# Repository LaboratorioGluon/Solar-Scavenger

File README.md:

# Solar Scavenger

Os presento el barco **Solar Scavenger** participante de la VI Regata Solar en Baiona!

El resultado: Primer premio en diseño y tercero en regata!

Todo está desarrollado en directo, desde la PCB, diseño 3D, software y montaje! (Link abajo)

## Materiales usados:

| Nombre | Descripción |
|---|---|
| [A2212 1000 KV](https://s.click.aliexpress.com/e/_DB0ZUoN) | Motor brushless outrunner para el barco|
| [ESC 4S 40A](https://s.click.aliexpress.com/e/_DB3iqU5) | Controlador de velocidad ESC |
| [ESP32](https://s.click.aliexpress.com/e/_DdJJJ5L) | Cerebro del controlador |

## PCB

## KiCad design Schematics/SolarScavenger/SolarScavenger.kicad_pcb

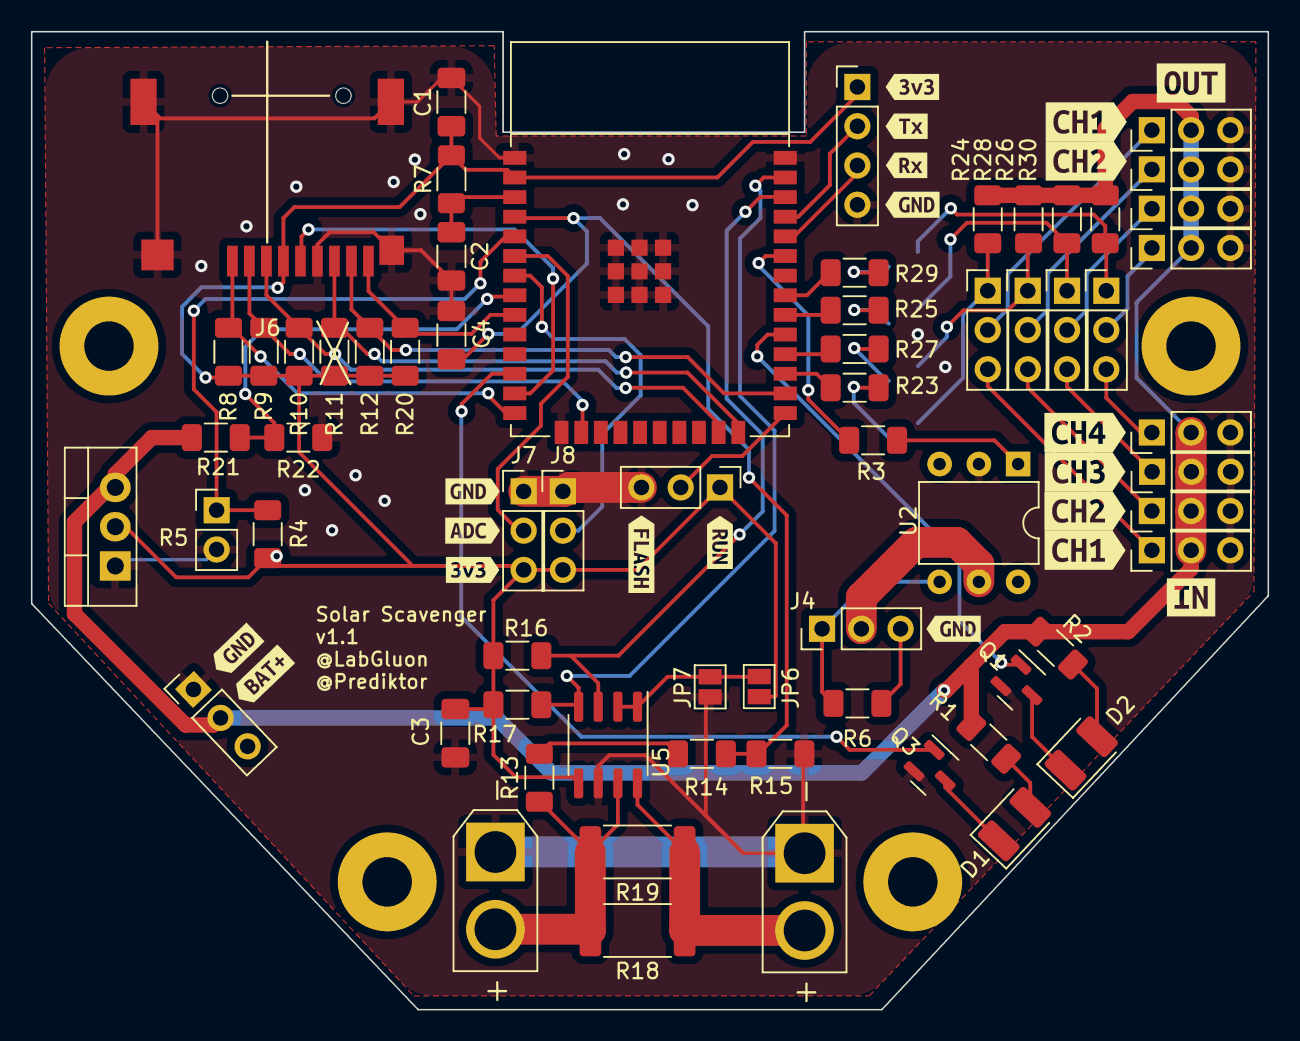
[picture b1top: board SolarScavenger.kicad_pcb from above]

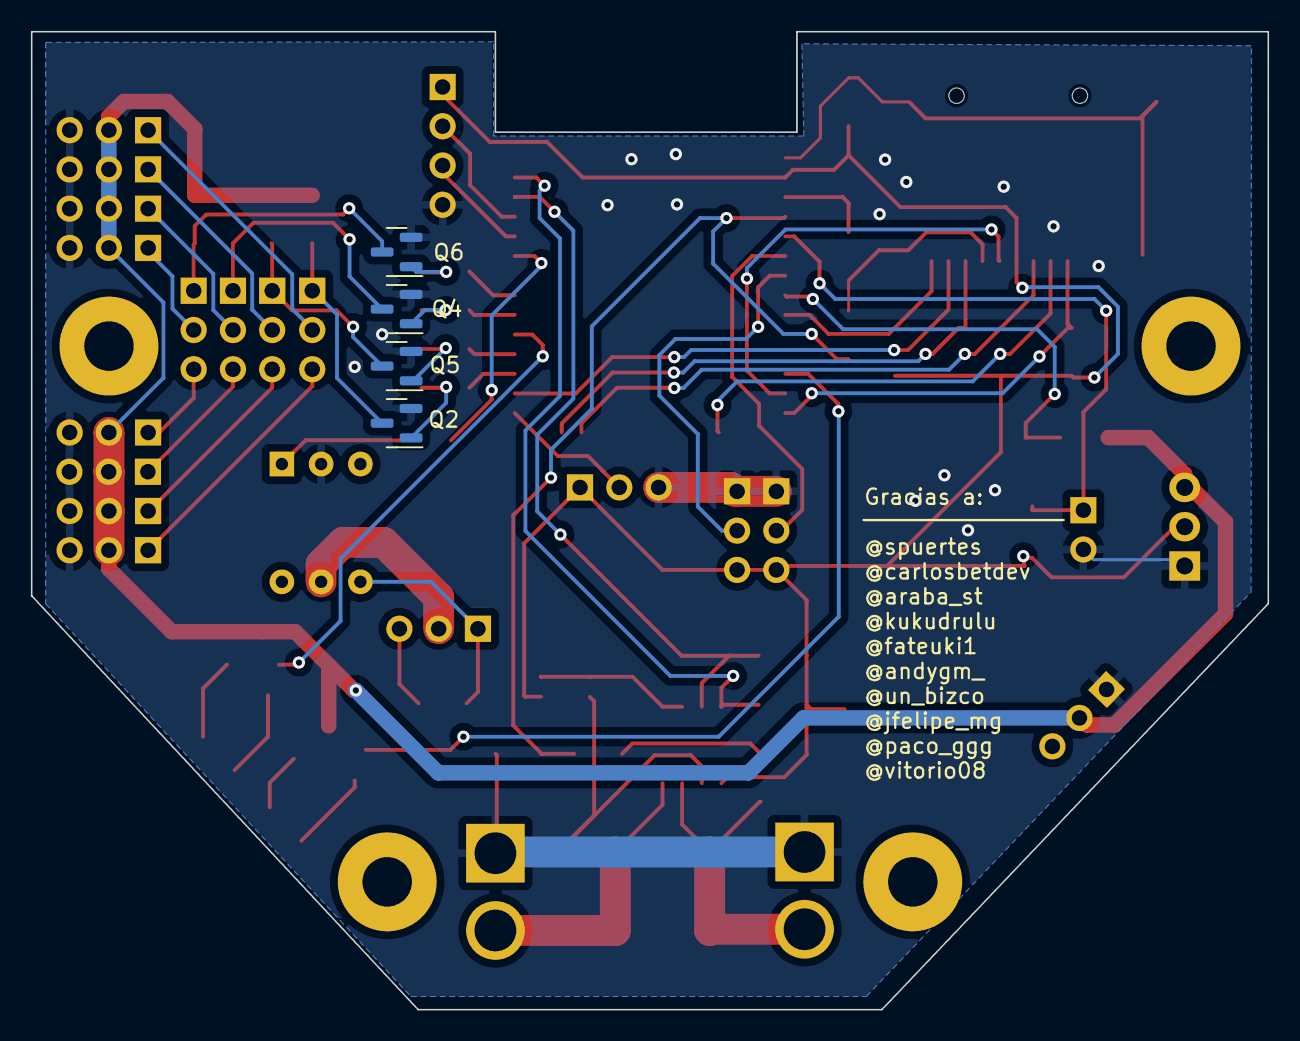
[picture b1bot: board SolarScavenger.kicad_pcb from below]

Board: 2 copper layers, 80.0 x 63.3 mm, 89 parts (4 on the bottom side), 56 nets.

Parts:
C1, C3: 47uF; C_1206_3216Metric_Pad1.33x1.80mm_HandSolder
C2, C4: 100nF; C_1206_3216Metric_Pad1.33x1.80mm_HandSolder
D1: LED_R; LED_1210_3225Metric_Pad1.42x2.65mm_HandSolder
D2: LED_G; LED_1210_3225Metric_Pad1.42x2.65mm_HandSolder
J1: SolarConnector; AMASS_XT30U-M_1x02_P5.0mm_Vertical
J2: PROGRAMMING; PinHeader_1x04_P2.54mm_Vertical
J3: BATTERY; PinHeader_1x03_P2.54mm_Vertical
J4: ESC_PWM_CONTROL; PinHeader_1x03_P2.54mm_Vertical
J5: ESC_connector; AMASS_XT30U-M_1x02_P5.0mm_Vertical
J6: Micro_SD_Card; microSD-Receptacle-SelfEject
J7: RUDDER_POT; PinHeader_1x03_P2.54mm_Vertical
J8: THROTTLE_POt; PinHeader_1x03_P2.54mm_Vertical
J17: CH1_IN; PinHeader_1x03_P2.54mm_Vertical
J18: CH1_OUT; PinHeader_1x03_P2.54mm_Vertical
J19: CH3_IN; PinHeader_1x03_P2.54mm_Vertical
J20: CH3_OUT; PinHeader_1x03_P2.54mm_Vertical
J21: CH2_IN; PinHeader_1x03_P2.54mm_Vertical
J22: CH2_OUT; PinHeader_1x03_P2.54mm_Vertical
J23: CH4_IN; PinHeader_1x03_P2.54mm_Vertical
J24: CH4_OUT; PinHeader_1x03_P2.54mm_Vertical
JP1: BOOT_SELECT; PinHeader_1x03_P2.54mm_Vertical
JP6: INA_A0; SolderJumper-2_P1.3mm_Open_Pad1.0x1.5mm
JP7: INA_A1; SolderJumper-2_P1.3mm_Open_Pad1.0x1.5mm
JP8: CH1_SERVO; PinHeader_1x03_P2.54mm_Vertical
JP9: CH3_SERVO; PinHeader_1x03_P2.54mm_Vertical
JP10: CH2_SERVO; PinHeader_1x03_P2.54mm_Vertical
JP11: CH4_SERVO; PinHeader_1x03_P2.54mm_Vertical
Q1, Q2, Q3, Q4, Q5, Q6: IRLM2502; SOT-23
R1: 680; R_1206_3216Metric_Pad1.30x1.75mm_HandSolder
R2: 2k2; R_1206_3216Metric_Pad1.30x1.75mm_HandSolder
R3: 220; R_1206_3216Metric_Pad1.30x1.75mm_HandSolder
R4: 4k7; R_1206_3216Metric_Pad1.30x1.75mm_HandSolder
R5: R_Photo; PinHeader_1x02_P2.54mm_Vertical
R6, R13, R14, R16, R17, R21, R22: 1k; R_1206_3216Metric_Pad1.30x1.75mm_HandSolder
R7, R8, R9, R10, R11, R12, R20: 10k; R_1206_3216Metric_Pad1.30x1.75mm_HandSolder
R15: 330; R_1206_3216Metric_Pad1.30x1.75mm_HandSolder
R18, R19: R100/2W; R_2512_6332Metric_Pad1.40x3.35mm_HandSolder
R23, R25, R27, R29: 100; R_1206_3216Metric_Pad1.30x1.75mm_HandSolder
R24, R26, R28, R30: 1K; R_1206_3216Metric_Pad1.30x1.75mm_HandSolder
U2: 4N25; DIP-6_W7.62mm
U3: AP1117-33; TO-220-3_Vertical
U4: ESP32-WROOM-E; ESP32-WROOM-32E
U5: INA219AxD; SOIC-8_3.9x4.9mm_P1.27mm
kibuzzard-63EE93D3: G***; kibuzzard-63EE93D3
kibuzzard-63EE93FE, kibuzzard-63EE93FE#2: G***; kibuzzard-63EE93FE
kibuzzard-63EE940D: G***; kibuzzard-63EE940D
kibuzzard-63EE941D: G***; kibuzzard-63EE941D
kibuzzard-63EE9448: G***; kibuzzard-63EE9448
kibuzzard-63F11AB2: G***; kibuzzard-63F11AB2
kibuzzard-63F11AB7: G***; kibuzzard-63F11AB7
kibuzzard-63F11AC7: G***; kibuzzard-63F11AC7
kibuzzard-63F11AD1: G***; kibuzzard-63F11AD1
kibuzzard-63F11F4E: G***; kibuzzard-63F11F4E
kibuzzard-63F11F5A: G***; kibuzzard-63F11F5A
kibuzzard-63F118E7: G***; kibuzzard-63F118E7
kibuzzard-63F118F7: G***; kibuzzard-63F118F7
kibuzzard-63F127EF: G***; kibuzzard-63F127EF
kibuzzard-63F1280A: G***; kibuzzard-63F1280A
kibuzzard-63F12006: G***; kibuzzard-63F12006
kibuzzard-63F12026, kibuzzard-63F12026#2: G***; kibuzzard-63F12026
kibuzzard-63F12816: G***; kibuzzard-63F12816

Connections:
+3V3: C1.1, C3.1, J2.1, J6.4 (VDD), J7.3, J8.3, JP1.1 (A), JP6.1 (A), R4.1, R7.2, R8.2, R9.2, R10.2, R11.2, R12.2, R16.2, R17.2, R20.2, U3.2 (VO), U4.2 (3V3), U5.5 (VS)
+BATT: J3.2, J17.2, J18.2, J19.2, J20.2, J21.2, J22.2, J23.2, J24.2, R1.1, R2.1, R21.1, R24.2, R26.2, R28.2, R30.2, U3.3 (VI)
/SD_CLK: J6.5 (CLK), U4.13 (MTMS/GPIO14/ADC2_CH6)
/SD_CMD: J6.3 (CMD), R10.1, U4.23 (MTDO/GPIO15/ADC2_CH3)
/SD_DATA0: J6.7 (DAT0), R11.1, U4.24 (ADC2_CH2/GPIO2)
/SD_DATA1: J6.8 (DAT1), R12.1, U4.26 (ADC2_CH0/GPIO4)
/SD_DATA2: J6.1 (DAT2), R8.1, U4.14 (MTDI/GPIO12/ADC2_CH5)
/SD_DATA3: J6.2 (DAT3/CD), R9.1, U4.16 (MTCK/GPIO13/ADC2_CH4)
BATT_SENSOR: R21.2, R22.1, U4.8 (32K_XP/GPIO32/ADC1_CH4)
CH1_ESP: R23.1, U4.27 (GPIO16)
CH2_ESP: R27.1, U4.28 (GPIO17)
CH3_ESP: R25.1, U4.30 (GPIO18)
CH4_ESP: R29.1, U4.31 (GPIO19)
ESC_5V: J4.2, U2.5
ESC_GND: J4.3, R6.2
ESC_PWM: J4.1, R6.1, U2.4
ESP32_BOOT: JP1.2 (C), U4.25 (GPIO0/BOOT/ADC2_CH1)
INA_SCL: R17.1, U4.37 (GPIO23), U5.4 (SCL)
INA_SDA: R16.1, U4.36 (GPIO22), U5.3 (SDA)
LED_1: Q1.1 (G), U4.29 (GPIO5)
LED_2: Q3.1 (G), U4.12 (ADC2_CH7/GPIO27)
LIGHT_SENSOR: R4.2, R5.1, U4.5 (SENSOR_VN/GPIO39/ADC1_CH3)
MOTOR_SUPPLY_N: C1.2, C2.2, C3.2, C4.2, J1.1, J2.4, J3.1, J5.1, J6.6 (VSS), J6.11 (SHIELD), J7.1, J8.1, J17.3, J18.3, J19.3, J20.3, J21.3, J22.3, J23.3, J24.3, JP1.3 (B), JP7.1 (A), Q1.2 (S), Q2.2 (S), Q3.2 (S), Q4.2 (S), Q5.2 (S), Q6.2 (S), R5.2, R15.1, R22.2, U2.2, U3.1 (GND), U4.1 (GND), U4.15 (GND), U4.38 (GND), U4.39 (GND_THERMAL), U5.6 (GND)
MOTOR_SUPPLY_P: J5.2, R13.2, R18.2, R19.2, U5.7 (IN-)
MOTOR_VOLTAGE: C4.1, R14.1, R15.2, U4.4 (SENSOR_VP/GPIO36/ADC1_CH0)
unnamed: D1.2 (A), R1.2
unnamed: D1.1 (K), Q3.3 (D)
unnamed: D2.2 (A), R2.2
unnamed: D2.1 (K), Q1.3 (D)
unnamed: J17.1, JP8.3 (B)
unnamed: J18.1, JP8.2 (C)
unnamed: J19.1, JP9.3 (B)
unnamed: J20.1, JP9.2 (C)
unnamed: J21.1, JP10.3 (B)
unnamed: J22.1, JP10.2 (C)
unnamed: J23.1, JP11.3 (B)
unnamed: J24.1, JP11.2 (C)
unnamed: JP6.2 (B), JP7.2 (B), U5.1 (A1), U5.2 (A0)
unnamed: JP8.1 (A), Q2.3 (D), R24.1
unnamed: JP9.1 (A), Q4.3 (D), R26.1
unnamed: JP10.1 (A), Q5.3 (D), R28.1
unnamed: JP11.1 (A), Q6.3 (D), R30.1
unnamed: Q2.1 (G), R23.2
unnamed: Q4.1 (G), R25.2
unnamed: Q5.1 (G), R27.2
unnamed: Q6.1 (G), R29.2
unnamed: R3.2, U2.1
unnamed: R13.1, R14.2
unnamed: C2.1, R7.1, U4.3 (EN/CHIP_PU)
PWM_TO_ESC: R3.1, U4.33 (GPIO21)
RUDDER_ADC: J7.2, U4.6 (GPIO34/ADC1_CH6)
SUPPLY_IN_P: J1.2, R18.1, R19.1, U5.8 (IN+)
THROTTLE_ADC: J8.2, U4.7 (GPIO35/ADC1_CH7)
UART_RX: J2.3, U4.34 (U0RXD/GPIO3)
UART_TX: J2.2, U4.35 (U0TXD/GPIO1)
/CD_DETECT: J6.9 (CD), R20.1, U4.9 (32K_XN/GPIO33/ADC1_CH5)

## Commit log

2023-02-12 3d files v1
2023-02-12 Added stls for ship and propellers
2023-02-13 Boat top part heigth reduced to 2mm
2023-02-15 Bajado el margen de las juntas del casco a 0.5mm
2023-02-15 Primera version de 2 modos de MPPT, simulacion panel solar y pwm alfa
2023-02-18 Schematic update
2023-02-18 PCB final candidate
2023-02-18 Actual final canditate
2023-02-19 Update de los interfaces SW
2023-02-19 SW compiling correctly
2023-02-19 Working motor PWM
2023-02-20 Mppt and simul reworked to c++ style
2023-02-22 Increased margin to 1mm
2023-02-23 Version 1.0 de la PCB, enviada a fabricar
2023-02-23 Updated main
2023-02-26 Working COMMS example
2023-03-05 Comms working with throttle and rudder
2023-03-07 Added SD writter and updated for IDF 5.0
2023-03-20 Added SD and current sensor code
2023-03-23 PCB v1.1
2023-03-24 Added images and Readme
2023-04-07 First simulation
2023-04-07 Working SD and PWM inverted for new PCB
2023-04-18 Added bidirectional comms
2023-04-18 Minor cleanup
2023-04-18 Added timeout check in comms
2023-04-22 Added Check for comms and changed us for servo
2023-04-25 Added signal measurement and wifi long range enabled
2023-04-25 DB value sent to the EMISOR for display
2023-04-26 Minor fixes and added EMISOR mac to receive messages
2023-05-28 Working Alpha and renamed EMISOR/RECEPTOR to MANDO/BARCO
2023-05-28 Power is handled by MANDO too
2023-06-02 Fix MPPT not engaging
2023-06-11 Fix ESC PWM signal
2023-06-11 Con boton MPPT
2023-06-15 Disconection protection
2023-06-22 Update README.md
    Updated README with more info
2023-06-22 Updated STL files
